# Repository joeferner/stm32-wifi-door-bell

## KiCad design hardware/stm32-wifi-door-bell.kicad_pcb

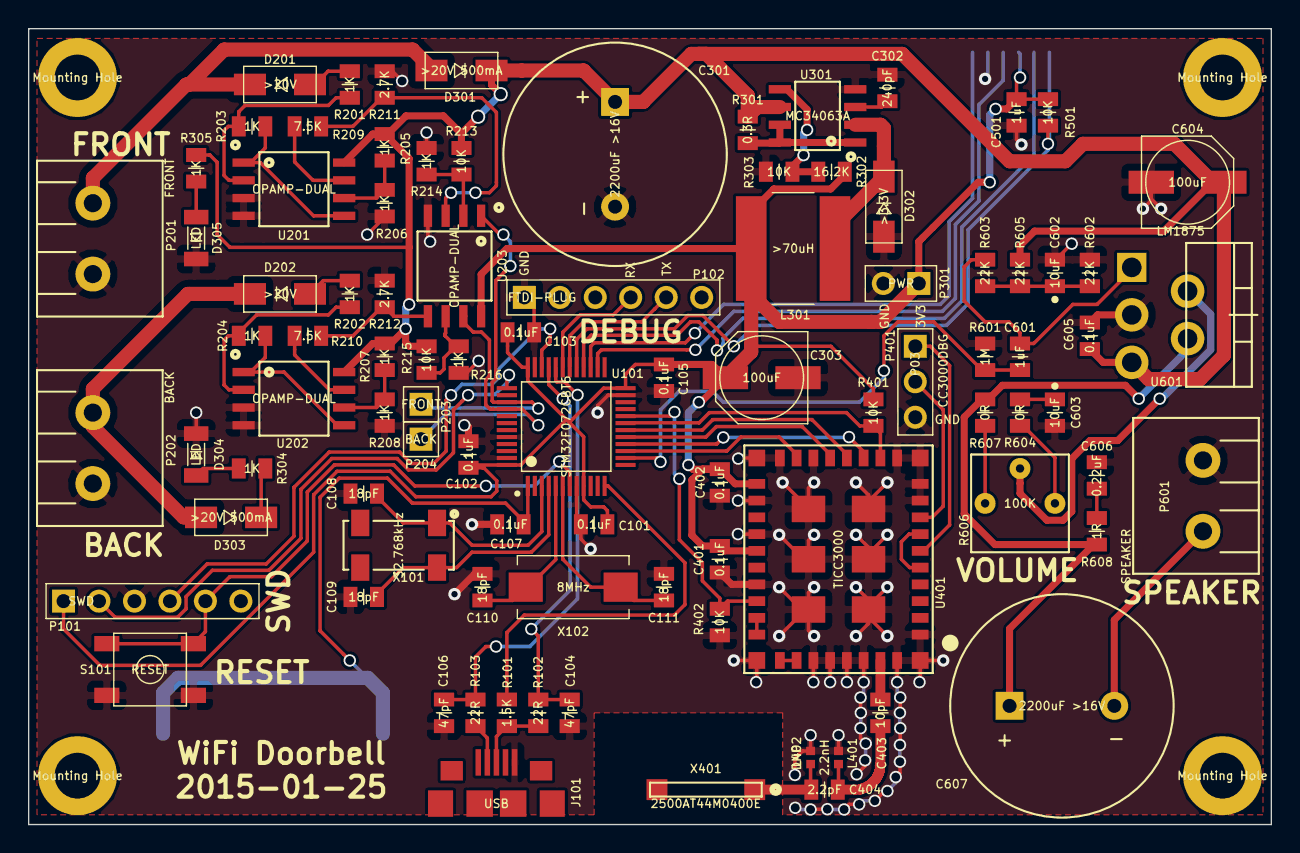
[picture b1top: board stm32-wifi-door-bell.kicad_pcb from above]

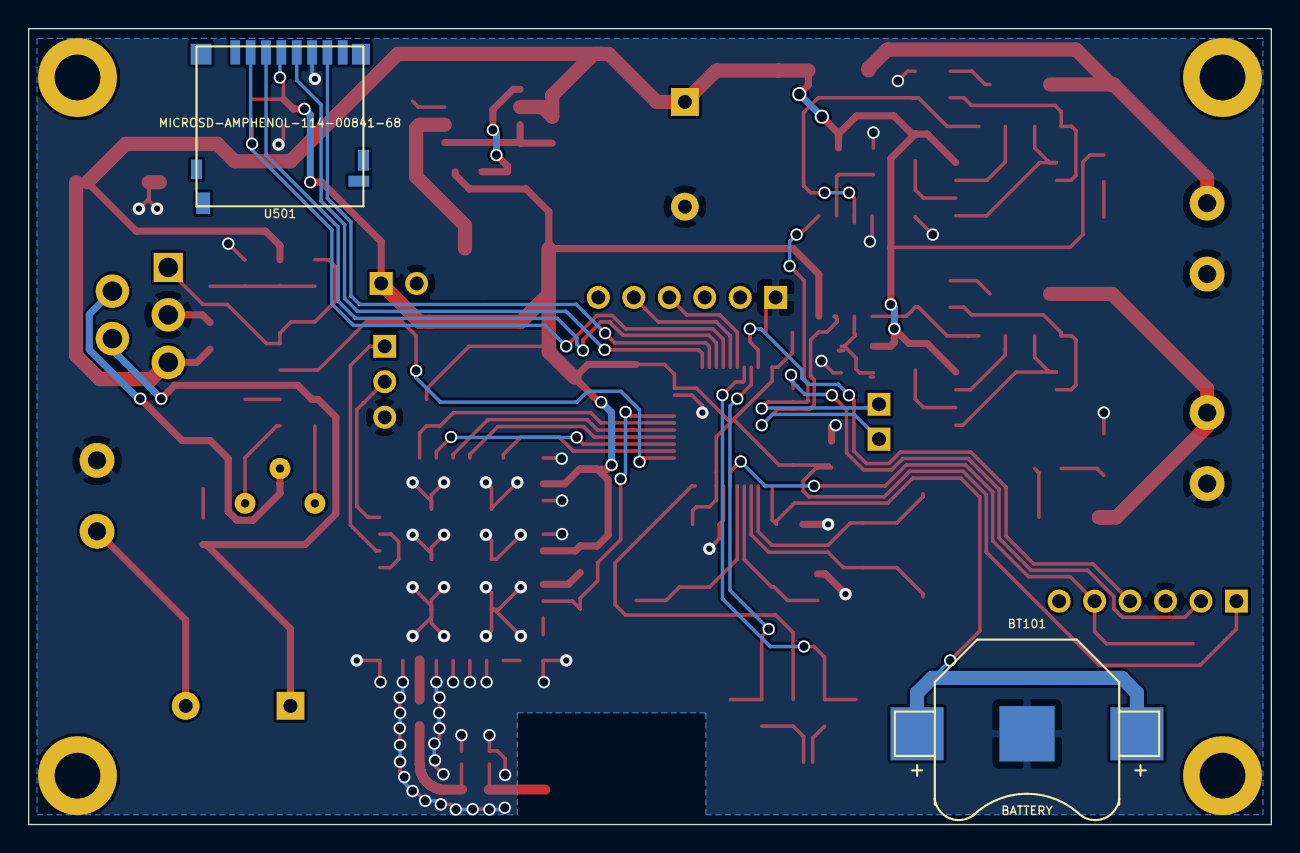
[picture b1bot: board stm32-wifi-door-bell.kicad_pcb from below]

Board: 2 copper layers, 89.0 x 57.0 mm, 98 parts (2 on the bottom side), 71 nets.

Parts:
BT101: BATTERY; KEYSTONE-3000
C101, C102, C103, C105, C107, C401, C402, C605: 0.1uF; CAPC2012X100N
C104, C106: 47pF; CAPC2012X100N
C108, C109, C110, C111: 18pF; CAPC2012X100N
C301, C607: 2200uF >16V; CAPPRD750W80D1600H2500P
C302: 240pF; CAPC2012X100N
C303, C604: 100uF; CAPAE660X790N
C403: 10pF; CAPC2012X100N
C404: 2.2pF; CAPC2012X100N
C501, C601: 1uF; CAPC2012X100N
C602, C603: 10uF; CAPCP2012X100N
C606: 0.22uF; CAPC2012X100N
D201, D202: >20V; DIOM5226X220N
D301, D303: >20V 500mA; DIOM5226X220N
D302: >3.3V; DIOM5226X220N
D304, D305: LED; LEDC3216X100N
J101: USB; JST_UB-MC5BR3-SD204-4S-NMP
L301: >70uH; IND_ASPI-8040S-680M-T
L401: 2.2nH; INDC1005X60N
L402: DNP; INDC1005X60N
M101, M102, M103, M104: Mounting Hole; MTGNP565H328Z565P
P101: SWD; HDRV6W66P254_1X6_1524X249X838P
P102: FTDI-PLUG; HDRV6W66P254_1X6_1524X249X838P
P201: FRONT; OST-OSTTA024163
P202: BACK; OST-OSTTA024163
P203: FRONT; HDRV1W66P254_1X1_254X249X838P
P204: BACK; HDRV1W66P254_1X1_254X249X838P
P301: PWR; HDRV2W66P254_1X2_508X249X838P
P401: P03; HDRV3W66P254_1X3_762X249X838P
P601: SPEAKER; OST-OSTTA024163
R101: 1.5K; RESC2012X100N
R102, R103: 22R; RESC2012X100N
R201, R202, R203, R204, R205, R206, R207, R208, R214, R216, R304, R305: 1K; RESC2012X100N
R209, R210: 7.5K; RESC2012X100N
R211, R212: 2.7K; RESC2012X100N
R213, R215, R303, R401, R402, R501: 10K; RESC2012X100N
R301: 0.3R; RESC2012X100N
R302: 16.2K; RESC2012X100N
R601: 1M; RESC2012X100N
R602, R603, R605: 22K; RESC2012X100N
R604, R607: 0R; RESC2012X100N
R606: 100K; COPAL-CT6EP
R608: 1R; RESC2012X100N
S101: RESET; CKCOMP-PTS525SM10SMTR
U101: STM32F072CBT6; QFP50P900X900X160-48N
U201, U202, U203: OPAMP-DUAL; SOIC127P790X216-8N
U301: MC34063A; SOIC127P600X175-8N
U401: TICC3000; TI-CC3000
U501: MICROSD-AMPHENOL-114-00841-68; AMPHENOL-114-00841-68
U601: LM1875; TO170P470X1028X2117-5P
X101: 32.768kHz; SOJ550P370X240-4N
X102: 8MHz; XTAL8045X200N
X401: 2500AT44M0400E; JT-2500AT44M0400E

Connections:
+3.3V: C101.1, C102.1, C103.1, C105.1, C303.1, C401.1, C402.1, C501.1, L301.2, P101.1, P301.1, R302.2, R401.2, R501.2, U101.9, U101.24, U101.36, U101.48, U203.8, U401.19, U401.23, U501.4
/DEBUGRX: P102.4, U101.31
/DEBUGTX: P102.5, U101.30
/SWCLK: P101.2, U101.37
/SWDIO: P101.4, U101.34
/USBDM: J101.2, R103.2
/USBDP: J101.3, R101.2, R102.2
/USBDPPU: R101.1, U101.12
/audio/AUDIOIN: C601.2, R601.1, U101.14
/input/BACKDIGITAL: P204.1, U101.40, U203.7
/input/BACKIN: D202.2, D303.1, P202.1
/input/FRONTDIGITAL: P203.1, U101.39, U203.1
/input/FRONTIN: D201.2, D301.1, P201.1
/nRST: P101.5, S101.3, S101.4, U101.7
/sdcard/CLK: U101.26, U501.5
/sdcard/CS: R501.1, U101.29, U501.2
/sdcard/SPIMISO: U101.27, U501.7
/sdcard/SPIMOSI: U101.28, U501.3
/wifi/ANT-NET-0: C403.1, U401.35
/wifi/ANT-NET-1: C403.2, C404.1, L401.1
/wifi/ANT-NET-2: C404.2, L402.1, X401.1
/wifi/CC3000RX: P401.2, U401.8
/wifi/CC3000TX: P401.1, U401.6
/wifi/CS: R401.1, U101.19, U401.12
/wifi/EN: R402.2, U101.20, U401.26
/wifi/IRQ: U101.18, U401.14
/wifi/SPICLK: U101.15, U401.17
/wifi/SPIMISO: U101.16, U401.13
/wifi/SPIMOSI: U101.17, U401.15
GNDPWR: BT101.2, C101.2, C102.2, C103.2, C104.1, C105.2, C106.1, C107.2, C108.2, C109.2, C110.2, C111.2, C301.2, C302.2, C303.2, C401.2, C402.2, C501.2, C602.2, C603.2, C604.2, C605.2, C606.2, D302.1, D304.2, D305.2, J101.5, L401.2, L402.2, P101.3, P102.1, P201.2, P202.2, P301.2, P401.3, P601.2, R206.2, R208.2, R211.1, R212.1, R214.1, R216.1, R303.1, R402.1, R601.2, R602.1, S101.1, S101.2, U101.8, U101.23, U101.35, U101.44, U101.47, U201.3, U201.4, U202.3, U202.4, U203.4, U301.4, U401.1, U401.9, U401.10, U401.11, U401.16, U401.18, U401.20, U401.22, U401.25, U401.31, U401.32, U401.33, U401.34, U401.36, U401.37, U401.38, U401.39, U401.40, U401.41, U401.42, U401.43, U401.44, U401.45, U401.46, U501.6, U601.3
unnamed: BT101.1, C107.1, U101.1
unnamed: C104.2, R102.1, U101.33
unnamed: C106.2, R103.1, U101.32
unnamed: C108.1, U101.3, X101.1
unnamed: C109.1, U101.4, X101.4
unnamed: C110.1, U101.5, X102.1
unnamed: C111.1, U101.6, X102.2
unnamed: C302.1, U301.3
unnamed: C601.1, R603.2, U601.1
unnamed: C602.1, R602.2, R603.1, R605.2
unnamed: C603.1, R604.1
unnamed: C606.1, R608.2
unnamed: C607.1, R607.1, R608.1, U601.4
unnamed: C607.2, P601.1
unnamed: D201.1, R201.1
unnamed: D202.1, R202.1
unnamed: D302.2, L301.1, U301.2
unnamed: D303.2, R304.2
unnamed: D304.1, R304.1
unnamed: D305.1, R305.1
unnamed: R201.2, R203.1, U201.2
unnamed: R202.2, R204.1, U202.2
unnamed: R203.2, U201.1, U201.5
unnamed: R204.2, U202.1, U202.5
unnamed: R205.2, R206.1, U201.6
unnamed: R207.2, R208.1, U202.6
unnamed: R209.1, R211.2, U203.3
unnamed: R209.2, U201.7
unnamed: R210.1, R212.2, U203.5
unnamed: R210.2, U202.7
unnamed: R213.1, R214.2, U203.2
unnamed: R215.1, R216.2, U203.6
unnamed: R301.2, U301.1, U301.7, U301.8
unnamed: R302.1, R303.2, U301.5
unnamed: R604.2, R606.3
unnamed: R606.1, R607.2
unnamed: R606.2, U601.2
unnamed: U401.5, U401.7
unnamed: U401.27, U401.28
unnamed: U401.29, U401.30
Vcc: C301.1, C604.1, C605.1, D301.2, R205.1, R207.1, R213.2, R215.2, R301.1, R305.2, R605.1, U201.8, U202.8, U301.6, U601.5

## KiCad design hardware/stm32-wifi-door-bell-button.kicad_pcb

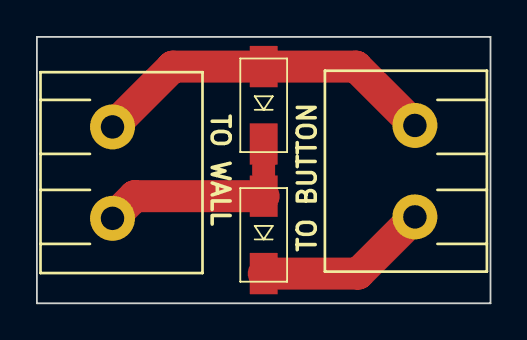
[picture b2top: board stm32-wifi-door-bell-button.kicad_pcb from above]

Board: 2 copper layers, 25.2 x 14.8 mm, 4 parts (0 on the bottom side), 3 nets.

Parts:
D101, D102: DIODESCH; DIOM5226X220N
P101: TRANSFORMER; OST-OSTTA024163
P102: BUTTON; OST-OSTTA024163

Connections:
unnamed: D101.1, P101.1, P102.2
unnamed: D101.2, D102.1, P101.2
unnamed: D102.2, P102.1

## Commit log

2014-12-15 initial
2014-12-15 working printf
2014-12-16 initial sd card reading
2014-12-16 move stm32lib files to directory
2014-12-16 seperate sdcard setup from gpio setup
2014-12-16 sdcard write
2014-12-17 fat compiles
2014-12-17 refactor names
2014-12-17 more refactors
2014-12-17 remove unused files
2014-12-17 sdcard read working
2014-12-18 wifi compiles
2014-12-18 working connect
2014-12-18 print ip address
2014-12-18 read config from sdcard
2014-12-18 add readme
2014-12-18 display mac address
2014-12-19 rtc and ntp working
2014-12-21 use profiles for faster connect
2014-12-22 working broadcast
2014-12-22 default name
2015-01-10 try to add polarssl
2015-01-10 button simulation
2015-01-10 add device id placeholder to config.ini
2015-01-10 broadcast button events
2015-01-10 update schematic
2015-01-11 more schematic work
2015-01-11 reannotate schematic
2015-01-15 more schematics
2015-01-18 initial layout
2015-01-18 fix erc and drc errors
2015-01-23 clean up pcb
2015-01-25 v20150125
2015-01-25 add polarity to big caps
2015-01-31 add speaker
2015-01-31 door bell button schematic
2015-02-09 initial try
2015-02-23 initial firmware rewrite
2015-02-23 read config
